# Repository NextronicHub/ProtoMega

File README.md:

# Nextronic ProtoMega

The ProtoMega is an Arduino mega prototyping shield with a soldering area, two LEDs, and the reset switch 
<br />This board is based on the sparkfun [MegaShield kit](https://www.sparkfun.com/products/9346).

##Repository Contents

/Hardware - Design files (.brd, .sch)
<br />/Documentation - datasheet and examples

##Product Versions

ProtoMega_V1 first release

##License Information

The hardware is released under [Creative Commons ShareAlike 4.0 International](https://creativecommons.org/licenses/by-sa/4.0/).

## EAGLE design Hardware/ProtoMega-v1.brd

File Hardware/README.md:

#  Nextronic ProtoMega Design Files

The .sch and .brd files are Eagle CAD schematic and PCB design files from Nextronic.  
Eagle PCB Design | Schematic Editor, Layout Editor & Autorouter can be found at http://www.autodesk.com/products/eagle.

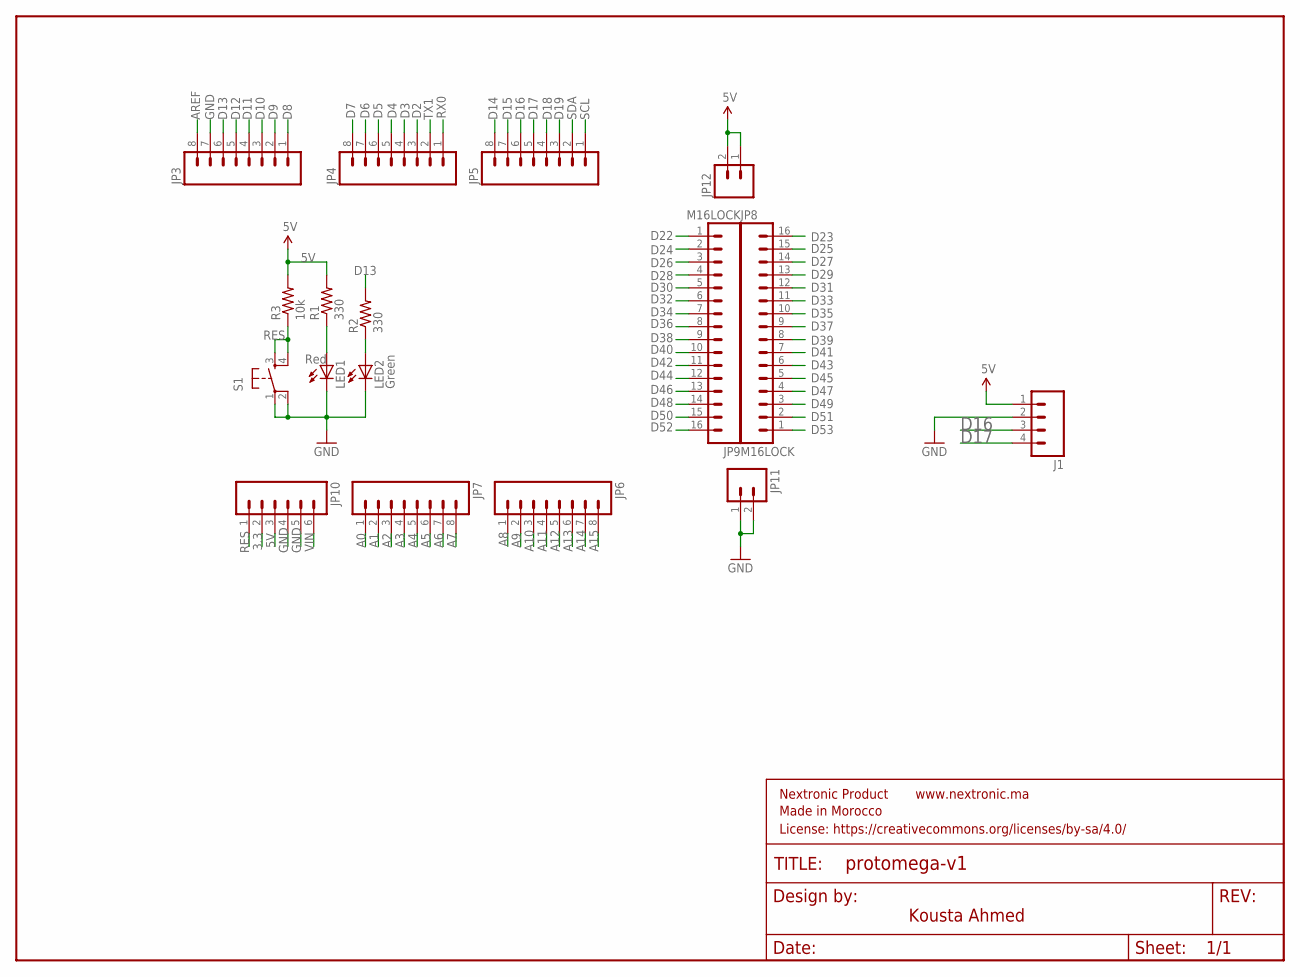
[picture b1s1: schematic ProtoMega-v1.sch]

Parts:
FRAME1: FRAME-LETTER; CREATIVE_COMMONS
J1: M04PTH; 1X04
JP3, JP4, JP5, JP6, JP7: M08LOCK; 1X08_LOCK
JP8, JP9: M16LOCK; 1X16_LOCK
JP10: M06LOCK; 1X06_LOCK
JP11, JP12: M02LOCK; 1X02_LOCK
LED1: Red; LED5MM
LED2: Green; LED5MM
R1, R2: 330; AXIAL-0.3
R3: 10k; AXIAL-0.3
S1: TAC_SWITCHPTH; TACTILE-PTH

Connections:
3.3: JP10.2
5V: J1.1, JP10.3, JP12.2, R1.P$2 (2), R3.P$2 (2)
5V@1: JP12.1
A0: JP7.1
A1: JP7.2
A2: JP7.3
A3: JP7.4
A4: JP7.5
A5: JP7.6
A6: JP7.7
A7: JP7.8
A8: JP6.1
A9: JP6.2
A10: JP6.3
A11: JP6.4
A12: JP6.5
A13: JP6.6
A14: JP6.7
A15: JP6.8
AREF: JP3.8
D2: JP4.3
D3: JP4.4
D4: JP4.5
D5: JP4.6
D6: JP4.7
D7: JP4.8
D8: JP3.1
D9: JP3.2
D10: JP3.3
D11: JP3.4
D12: JP3.5
D13: JP3.6, R2.P$2 (2)
D14: JP5.8
D15: JP5.7
D16: J1.3, JP5.6
D17: J1.4, JP5.5
D18: JP5.4
D19: JP5.3
D22: JP9.1
D23: JP8.16
D24: JP9.2
D25: JP8.15
D26: JP9.3
D27: JP8.14
D28: JP9.4
D29: JP8.13
D30: JP9.5
D31: JP8.12
D32: JP9.6
D33: JP8.11
D34: JP9.7
D35: JP8.10
D36: JP9.8
D37: JP8.9
D38: JP9.9
D39: JP8.8
D40: JP9.10
D41: JP8.7
D42: JP9.11
D43: JP8.6
D44: JP9.12
D45: JP8.5
D46: JP9.13
D47: JP8.4
D48: JP9.14
D49: JP8.3
D50: JP9.15
D51: JP8.2
D52: JP9.16
D53: JP8.1
GND: J1.2, JP3.7, JP10.4, JP10.5, JP11.1, JP11.2, LED1.K (C), LED2.K (C), S1.1, S1.2
unnamed: LED1.A, R1.P$1 (1)
unnamed: LED2.A, R2.P$1 (1)
RES: JP10.1, R3.P$1 (1), S1.3, S1.4
RX0: JP4.1
SCL: JP5.1
SDA: JP5.2
TX1: JP4.2
VIN: JP10.6

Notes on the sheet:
Kousta Ahmed

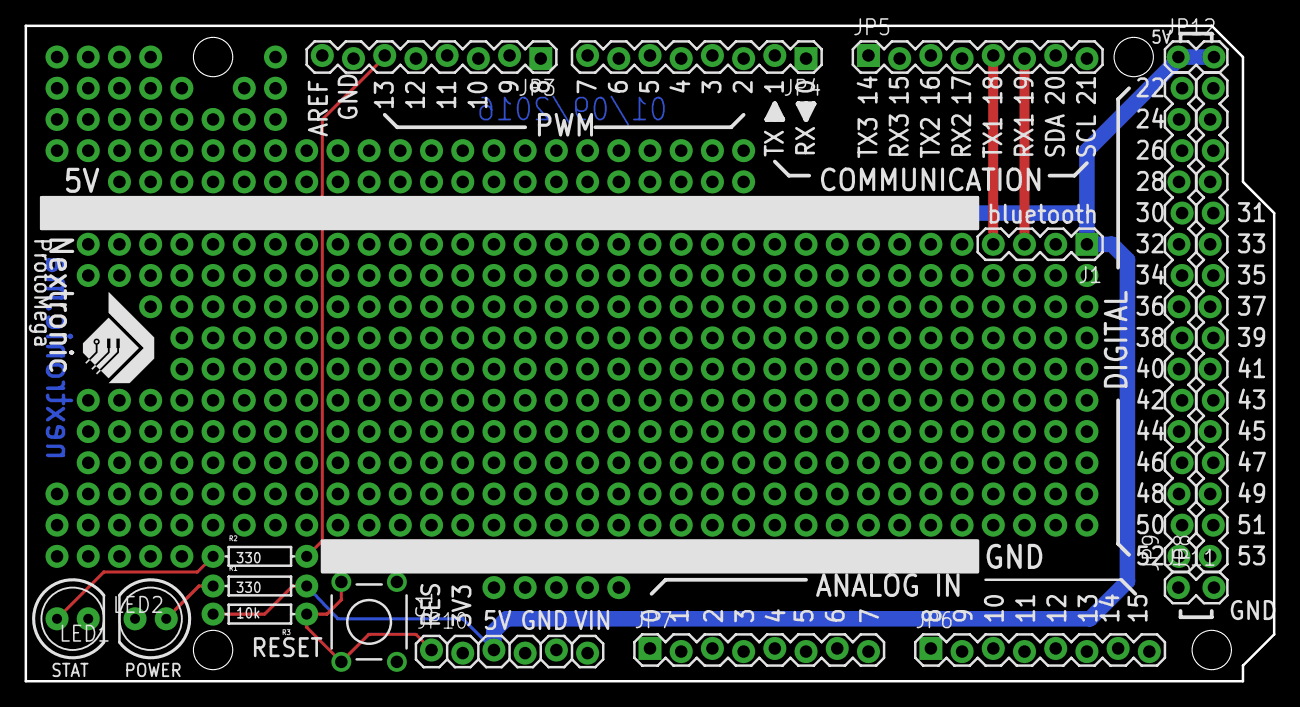
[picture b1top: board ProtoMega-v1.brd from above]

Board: 2 copper layers, 101.6 x 53.3 mm, 18 parts (0 on the bottom side), 8 nets.

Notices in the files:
parts and their libraries:
SparkFun-Aesthetics: Licensing: Creative Commons ShareAlike 4.0 International - https://creativecommons.org/licenses/by-sa/4.0
SparkFun-Aesthetics: License: https://creativecommons.org/licenses/by-sa/4.0
